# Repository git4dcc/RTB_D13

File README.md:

# RTB_D13

My Homebrew [D13](https://rtb4dcc.de/hardware/decoder/d13/) LED decoder is a drop in design for Minitrix (#15791) coach with no mechanical modification required. The decoder is designed to integrate into the [RTB](https://rtb4dcc.de/concept/) digital control infrastructure.

<details>
<summary>See also</summary>

- [RTB_D12 - custom](/../../../../git4dcc/RTB_D12) (Fleischmann V100)
- [RTB_D15 - custom](/../../../../git4dcc/RTB_D15) (Minitrix V160)
- [RTB_D16 - NEM651](/../../../../git4dcc/RTB_D16)
- [RTB_D20 - NEM651](/../../../../git4dcc/RTB_D20)
- [RTB_D21 - Next18](/../../../../git4dcc/RTB_D21)
- [RTB_D22 - Plux16](/../../../../git4dcc/RTB_D22)
- [RTB_D23 - NEM652](/../../../../git4dcc/RTB_D23)

</details>

<details>
<summary>User Guides</summary>

- User Guide - DE
- [User Guide - EN](https://rtb4dcc.de/rtb_decoder_reference_en/)

</details>

<br>

## Decoder features
- **DCC**
  - DCC-A automatic logon
  - DCC-R protocol extension
  - Service Mode Programming
- **Railcom**
  - Channel 1/2
  - POM, xPOM
  - DYN: QoS, Track-Voltage, Scap-Voltage, Temp, Ambient light
- 1x4F/2.8V SCAP (on PCB)
- Inrush limited
- step up/down converter
- max track voltage 25V
- Corridor (11 LEDs), Cabin (13 LEDs), Lavatory (2 LEDs)
- Status LEDs: heartbeat, charging, no-power
- motion sensor
- ambient light sensor
- fast firmware update within seconds on main tracks via DCC-R

# Hardware
The current PCB layout uses SMD footprints with 0.5mm pitch and mainly 0603 parts. Reflow soldering is recommended whereas handsoldering will be difficult.

## PCB
- 4-layer PCB, FR4, 1mm
- CPU: AVR64DA48

## Kicad
[Schematic](doc/D13_schematic.pdf) | [Layout](doc/D13_layout.pdf) | [Gerber](gerber)

<details>
<summary>Dependency</summary>
<br>

:yellow_circle: Requires my Kicad project library [RTB_SamacSys](https://github.com/git4dcc/RTB_SamacSys) in the same directory tree.

</details>

## Firmware
Filename structure: { **pcb** }{ **code** }{ **version** }.hex

Example: **D13F0001**.hex

|   | Description |
| --- | --- |
| **pcb** | Name of matching hardware (**D13**) |
| **code** | Type of code contained (**R**=rom, **B**=bootloader, **F**=flash, **U**=bld update, **P**=UPDI factory code) |
| **version** | Release version (**####**) |

[Firmware files](firmware)

# Images

# YouTube
See the D13 decoder in action.<br><br>

This project is intended for hobby use only and is distributed in accordance with the Apache License 2.0 agreement.

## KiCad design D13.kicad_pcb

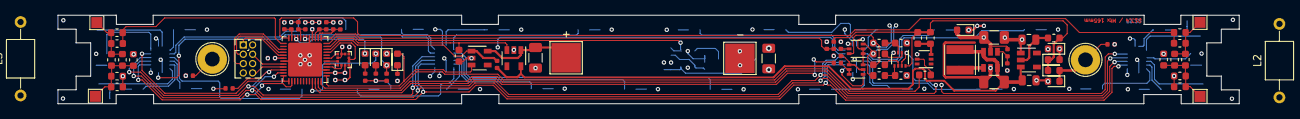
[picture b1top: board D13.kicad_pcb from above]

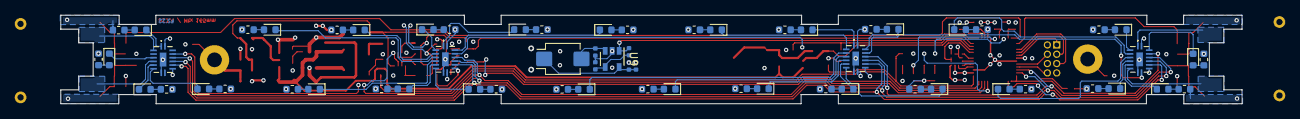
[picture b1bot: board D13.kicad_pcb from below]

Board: 4 copper layers, 160.8 x 12.0 mm, 153 parts (63 on the bottom side), 117 nets.

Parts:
C1, C5, C6, C7, C13, C21: 1u; C_0402_1005Metric
C2: <=100uF/4V; C_1206_3216Metric
C3: 4.7u; C_0805_2012Metric
C4: 220uF/6V; C_1206_3216Metric
C8: 4.7u/35V; C_0805_2012Metric
C9, C17: 22pF; C_0603_1608Metric
C10: 22u/25V; C_1206_3216Metric
C12: 220uF/4V; C_1206_3216Metric
C14, C18: 47pF; C_0603_1608Metric
C15, C19: 100pF; C_0603_1608Metric
C16, C20: 100nF; C_0603_1608Metric
D1: CDBU0245-HF; D_0603_1608Metric
D2, D3, D4: D_Schottky; D_0603_1608Metric
D5, D6, D7, D8, D9, D10, D11, D12, D14, D15, D16, D17, D18, D19, D20, D21, D22, D23, D24, D25, D26, D27, D28, D29, D30, D31, D32, D33, D34, D35: LED; LED_0603_1608Metric
D13: SFH2440; Osram_SMD-DIL2_4.5x4.0mm
D36: CDBURT0530LL-HF; D_0603_1608Metric
IC1: BMA255; LGA-12_2x2mm_P0.5mm
J2, J3: Conn_01x01; TestPoint_THTPad_D4.0mm_Drill2.0mm
J5: UDPI; PinHeader_2x04_P1.27mm_Vertical
L1: 4.7uH; L_Taiyo-Yuden_MD-4040
L2, L3: 150uH; L_Axial_L5.0mm_D3.6mm_P10.00mm_Horizontal_Murata_BL01RN1A2A2
Q1, Q3: BC847BDW1; SOT-363_SC-70-6
Q2: BC857BDW1; SOT-363_SC-70-6
R1: 100; R_0603_1608Metric
R2, R16: 22; C_0402_1005Metric
R3, R77: 6.8k; C_0402_1005Metric
R4: 10k; C_0402_1005Metric
R5, R6, R7, R8, R9, R10, R11, R12, R45, R46, R47, R48, R49, R50, R51, R52, R53, R54, R55, R56, R57, R58, R59, R60, R63, R64: 4.7k; C_0603_1608Metric
R13: 3.3k; R_0603_1608Metric
R14, R71: 470; R_0603_1608Metric
R15, R75: 10k; R_0402_1005Metric
R17: 47k; C_0603_1608Metric
R18, R19, R20, R21: 1k; C_0603_1608Metric
R22, R23: 100k; C_0603_1608Metric
R24, R26: 330k; R_0402_1005Metric
R25: 22k; R_0402_1005Metric
R27, R29, R30, R32: 100k; R_0603_1608Metric
R28, R31: 120k; R_0603_1608Metric
R35, R39, R43: 220k; R_0402_1005Metric
R36, R40, R44: 9.1k; R_0402_1005Metric
R37, R73: 47k; R_0402_1005Metric
R38, R62, R65, R66, R74: R; R_0402_1005Metric
R61: 1k; R_0402_1005Metric
R69: 1.69M; R_0402_1005Metric
R70: 1M; R_0402_1005Metric
R72: 100k; R_0402_1005Metric
TP1, TP2, TP3, TP4: TestPoint; TestPoint_Pad_1.5x1.5mm
TP5, TP6: TestPoint; TestPoint_Pad_4.0x4.0mm
U1: AVR-64DA48; UQFN-48-1EP_6x6mm_P0.4mm_EP4.62x4.62mm
U2, U3, U4, U5: 74HC595; 74HC595BQ115
U6: MCP1640BCH; SOT-23-6
U7: ST732; SOT-23-5
U8: LM393; DFN-8-1EP_NG_2x2mm_Pitch0.5mm
U9: MCP6001x-LT; SOT-23-5
U10, U11: MAX40203AUK; SOT-23-5

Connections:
+3V3: C1.2, C4.1, C5.2, C6.2, C7.2, C13.2, D36.1, IC1.3, IC1.7, J5.2, Q2.1, R2.1, R5.1, R6.1, R7.1, R8.1, R9.1, R10.1, R11.1, R12.1, R22.1, R23.1, R28.2, R31.2, R45.1, R46.1, R47.1, R48.1, R49.1, R50.1, R51.1, R52.1, R53.1, R54.1, R55.1, R56.1, R57.1, R58.1, R59.1, R60.1, R61.2, R62.1, R63.1, R64.1, R65.1, R66.1, R72.1, U1.14, U1.28, U1.42, U2.10, U2.16, U3.10, U3.16, U4.10, U4.16, U5.10, U5.16
ACK: R13.1, U1.12
BMA.cs: IC1.10, U1.19
BMA.int: IC1.5, IC1.6, U1.21
BMA.miso: IC1.1, U1.17
BMA.mosi: IC1.2, U1.16
BMA.sclk: IC1.12, U1.18
BUSa: C9.2, R27.2, U1.37
BUSb: C17.2, R30.2, U1.36
DCC-a: D1.2, D2.1, J2.1, Q1.3, R15.2, R18.1, R21.1, R35.1, R37.2
DCC-b: D3.2, D4.1, J3.1, Q1.6, R19.1, R20.1, R38.2, R39.1, R75.2
GND: C1.1, C2.2, C3.2, C4.2, C5.1, C6.1, C7.1, C8.2, C10.2, C12.2, C13.1, C16.2, C20.2, C21.2, D2.2, D4.2, D31.1, IC1.4, IC1.8, IC1.9, IC1.11, J5.6, Q1.4, Q3.4, R15.1, R17.2, R24.1, R25.1, R29.1, R32.1, R36.2, R40.2, R44.2, R70.1, R73.2, R74.2, R75.1, R77.2, TP6.1, U1.15, U1.29, U1.43, U1.49, U2.8, U3.8, U4.8, U5.8, U6.2, U7.1, U8.4, U9.2, U10.2, U11.2
LED.blu: D35.1, U1.33, U1.34
LED.ds: U1.1, U1.48, U2.14
LED.ds1: U2.9, U5.14
LED.ds2: U3.14, U5.9
LED.ds3: U3.9, U4.14
LED.grn: D32.1, U1.9
LED.red: D31.2, R62.2, U1.30, U1.31
LED.shcp: U1.2, U2.11, U3.11, U4.11, U5.11
LED.stcp: U1.47, U2.12, U3.12, U4.12, U5.12
unnamed: C2.1, TP5.1, U10.5, U11.1
unnamed: C8.1, R1.1, U7.2
unnamed: C10.1, D36.2, R69.2, U6.5
unnamed: C9.1, C14.1, C15.1, R27.1, TP1.1
unnamed: C14.2, C15.2, C16.1, R28.1, R29.2, TP2.1
unnamed: C17.1, C18.1, C19.1, R30.1, TP3.1
unnamed: C18.2, C19.2, C20.1, R31.1, R32.2, TP4.1
unnamed: C21.1, D13.1, R61.1, U9.5
unnamed: D5.1, U3.15
unnamed: D5.2, R5.2
unnamed: D6.1, U3.1
unnamed: D6.2, R6.2
unnamed: D7.1, U2.2
unnamed: D7.2, R7.2
unnamed: D8.1, U2.3
unnamed: D8.2, R8.2
unnamed: D9.1, U2.4
unnamed: D9.2, R9.2
unnamed: D10.1, U2.5
unnamed: D10.2, R10.2
unnamed: D11.1, U2.6
unnamed: D11.2, R11.2
unnamed: D12.1, U2.15
unnamed: D12.2, R12.2
unnamed: D13.2, R24.2, U9.3
unnamed: D14.1, R77.1
unnamed: D15.1, U5.15
unnamed: D15.2, R45.2
unnamed: D16.1, U5.1
unnamed: D16.2, R46.2
unnamed: D17.1, U5.3
unnamed: D17.2, R47.2
unnamed: D18.1, U5.2
unnamed: D18.2, R48.2
unnamed: D19.1, U5.4
unnamed: D19.2, R49.2
unnamed: D20.1, U5.5
unnamed: D20.2, R50.2
unnamed: D21.1, U5.6
unnamed: D21.2, R51.2
unnamed: D22.1, U5.7
unnamed: D22.2, R52.2
unnamed: D23.1, U3.2
unnamed: D23.2, R53.2
unnamed: D24.1, U3.3
unnamed: D24.2, R54.2
unnamed: D25.1, U3.4
unnamed: D25.2, R55.2
unnamed: D26.1, U3.5
unnamed: D26.2, R56.2
unnamed: D27.1, U3.6
unnamed: D27.2, R57.2
unnamed: D28.1, U3.7
unnamed: D28.2, R58.2
unnamed: D29.1, U4.1
unnamed: D29.2, R59.2
unnamed: D30.1, U4.4
unnamed: D30.2, R60.2
unnamed: D32.2, R65.2
unnamed: D33.1, U4.6
unnamed: D33.2, R63.2
unnamed: D34.1, U4.7
unnamed: D34.2, R64.2
unnamed: D35.2, R66.2
unnamed: L1.2, U6.1
unnamed: Q1.1, Q1.2, Q2.3, R3.1
unnamed: Q1.5, R3.2
unnamed: Q2.2, Q2.4, R2.2
unnamed: Q2.5, Q2.6, R4.1
unnamed: Q3.3, R14.1, R71.1
unnamed: Q3.5, R13.2
unnamed: R18.2, R22.2, U8.5
unnamed: R19.2, U8.6
unnamed: R20.2, R23.2, U8.3
unnamed: R21.2, U8.2
unnamed: R25.2, R26.2, U9.4
unnamed: R37.1, R73.1, U1.35
unnamed: R38.1, R74.1, U1.26
unnamed: R69.1, R70.2, U6.4
RCM.rx: U1.11, U8.1, U8.7
RCM.tx: R4.2, U1.10
SCAP_CHG: D14.2, U1.13, U10.3
SCAP_ENA: R17.1, U1.23, U11.3
UPDI: J5.1, U1.41
V24.cts: J5.3, U1.40
V24.rts: J5.5, U1.39
V24.rx: J5.8, U1.45
V24.tx: J5.4, U1.44
VLDO: C3.1, C12.1, L1.1, R16.2, U6.3, U6.6, U7.3, U11.5
VTRK: D1.1, D3.1, R1.2, R14.2, R43.1, R71.2, U8.8
uDCC-a: R35.2, R36.1, U1.32
uDCC-b: R39.2, R40.1, U1.27
uOPTO: R26.1, U1.24, U9.1
uSCAP: R16.1, U1.22, U10.1
uVTRK: R43.2, R44.1, U1.25
~LED.oe: R72.2, U1.46, U2.13, U3.13, U4.13, U5.13

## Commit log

2024-12-21 initial
2025-03-17 mod: LED animation
2025-03-21 add: supplemental files
2025-03-22 add: decoder lock
2025-08-05 mod: led automation
2026-02-20 Update links in README to relative paths
2026-02-20 git mirror test
